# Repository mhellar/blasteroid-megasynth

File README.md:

# BLASTEROID MEGASYNTH

**Experimental industrial ambient on an ESP32-S3.** A slow machine drone you build from layers, two robot mouths
(**SAM**, the 1982 Software Automatic Mouth, and the **Talkie** Speak & Spell LPC voice) that can freeze into drones,
get scratched on a knob and talk to each other, a box of industrial noises, and a huge reverb "space". It runs on a
4x4 keypad, one rotary pot, a 128x128 OLED and a small speaker.

At boot it plays a generative splash that's different every time: two random geometry scenes (string-art mandala,
polygon rings, flow-field particles, a rotating tunnel, a 3D Lissajous knot), glitch cuts. Then everything converges
into **the Blasteroid**: a cyborg cyclops in wraparound shades. His eye charges up, two lasers burn
**BLASTEROID / MEGASYNTH** in from opposite ends, SAM says the name, and Talkie answers "OPERATIONAL".

The board is a single-sided PCB designed to be **milled on a desktop CNC**. The modules plug into headers or edge
pads, so there's no SMD soldering.

## What's in here

| Folder | Contents |
|---|---|
| `firmware/blasteroid_megasynth/` | The Blasteroid Megasynth sketch (Arduino), with SAM's C core and the Talkie vocabularies bundled alongside |
| `firmware/keypad_bringup/` | Bring-up test: I2C scan, every key plays a note, pot = volume. Flash this first |
| `firmware/short_finder/` | Finds pins shorted to GND or to each other on a freshly milled board (pull-ups only, safe) |
| `hardware/kicad/` | KiCad project for the board (rev B: pot standing under the OLED), custom symbols + footprints |
| `hardware/cnc/` | Gerbers + drills, G-code for a Genmitsu Cubiko (GRBL), FlatCAM script, 1:1 fit-test print, cheat sheet |
| `tools/` | `splash_preview.py`: a Python mirror of the boot splash that renders storyboards (`python splash_preview.py <seed> <seconds...>`, needs numpy + Pillow) |

## Parts

| Ref | Part | Notes |
|---|---|---|
| U1 | ESP32-S3 **SuperMini** | 2x 1x9 female headers. Needs **PSRAM** (e.g. 4 MB flash / 2 MB PSRAM) |
| U2 | MAX98357A I2S amp breakout | 1x7 female header, VIN on 5 V, plus a small 4-8 ohm speaker |
| U3 | 1.5" 128x128 OLED, **SH1107**, I2C | 1x4 female header (VCC GND SCL SDA) |
| U4 | 4x4 tact keypad module (passive matrix, e.g. QYF-JP01) | hangs off the bottom edge; its right-angle pins lie on 8 edge pads |
| U5 | 10k rotary pot module (3 pins) | stands in 3 holes under the OLED, knob towards the keypad |
| | 100 x 70 mm single-sided copper clad | board is 96 x 66 mm, M3 holes |

## Pinout

| Function | GPIO |
|---|---|
| OLED SDA / SCL | 9 / 8 |
| Amp DIN / BCLK / LRC | 43 (TX) / 44 (RX) / 1 |
| Keypad rows R1-R4 / columns C1-C4 | 2 3 4 5 / 6 7 13 12 |
| Pot wiper / pot high leg | 10 / 11 (driven HIGH as the pot's supply), low leg to GND |

The amp uses the TX/RX pins, so **USB CDC On Boot must be Enabled** (serial goes over native USB).

## Build the firmware

1. Arduino IDE (or arduino-cli) with the **ESP32 core 3.x** and the **U8g2** library.
2. Board settings: **ESP32S3 Dev Module**, **USB CDC On Boot: Enabled**, **PSRAM: enabled**.
   arduino-cli FQBN: `esp32:esp32:esp32s3:CDCOnBoot=cdc,PSRAM=enabled`
3. Flash `keypad_bringup` first to check the keys, pot, OLED and speaker, then `blasteroid_megasynth`.

```
arduino-cli compile --fqbn esp32:esp32:esp32s3:CDCOnBoot=cdc,PSRAM=enabled firmware/blasteroid_megasynth
arduino-cli upload  --fqbn esp32:esp32:esp32s3:CDCOnBoot=cdc,PSRAM=enabled -p COMx firmware/blasteroid_megasynth
```

Tips:
- The OLED needs the `U8G2_SH1107_PIMORONI_128X128` constructor. The generic SH1107 one shifts the picture by 32 px.
- If the SuperMini sits silent after an upload, press RST. The auto-reset can leave it in the bootloader.
- If the knob works backwards, turn the pot module round. Swapping its outer legs reverses the direction.

## Playing it

```
[MODE ] [ pad 0 ] [ pad 1 ] [ pad 2 ]      left column: tap = quick action,
[FX   ] [ pad 3 ] [ pad 4 ] [ pad 5 ]      HOLD = the screen shows what the 12 pads do
[SEQ  ] [ pad 6 ] [ pad 7 ] [ pad 8 ]
[SHIFT] [ pad 9 ] [ pad 10] [ pad 11]
```

| Key | tap | hold + pad |
|---|---|---|
| MODE | next mode (HUM > SAM > TALK > MACH) | modes, volume, Talkie bank, **REPLAY** the boot film, SAM voice (ROBOT SAM GHOST DEEP) |
| FX | next voice FX | CLEAN ECHO RADIO GRAIN DEEP VOX CHOIR, momentary STUTTER / REVERSE / TAPE STOP / UNDERWATER, **INFINITE** (reverb freeze) |
| SEQ | REC on/off | PLAY, **CROSSTALK**, AUTO, BPM -/+, MUTATE, RANDOM machines (sparse > busy > factory), clears, SILENCE |
| SHIFT | PLAY/STOP | per mode: drone octave / brightness / LFO speed / detune; SAM words backwards; Talkie bends; machine mutes |

**The knob**
- **Knob alone:** the current voice FX's main control: pitch, echo feedback, radio tuning, grain density, depth, vocoder wet, choir breath.
- **SHIFT + knob = SCRATCH:** scrub through the current SAM or Talkie word like a record under your hand. It's silent while the knob is still.
- **FX + knob = SPACE:** from dry and close to a huge, long reverb.

**Modes**
- **HUM:** drone layers on/off: MAINS (transformer hum), SUB, PAD, CHOIR (morphing vowel), METAL (inharmonic FM girder), WIND, RADIO (shortwave whistle and crackle), PULSE (heartbeat). Also DRIFT (the chord wanders i-bVI-bIII-bVII), KEY -/+, and CHORD (fifth, minor7, sus2, minor9, void).
- **SAM:** 12 words (OHM, SILENCE, SIGNAL, MACHINE, BREATHE, ECHO, VOID, DRIFT, STATIC, RESONANCE, FREQUENCY, WE ARE LISTENING). Tap = say it, hold = **freeze** it into a granular drone.
- **TALK:** four Talkie banks: SIGNAL, NUMBERS (numbers station), ELEMENTS, MACHINE. Tap = say it, hold = freeze the mouth on one frame, humming in the drone's key.
- **MACH:** 12 industrial sounds: KLANK, PIPE, HAMMER, HISS, GEIGER, RELAY, SERVO, SONAR, CHAIN, DRIP, HORN, THUD. Hold = repeat.
- **CROSSTALK:** SAM and Talkie take turns, a word per bar, over whatever is playing.
- With REC on, voices and machines are quantized into the 16-step sequencer.

## Make the board

Single-sided, all copper on **B.Cu**, made for isolation milling. The Gerbers also work at a board house as a 1-layer board.
Full steps are in `hardware/cnc/CNC_CHEATSHEET.txt`: V-bit isolation, 1.0 mm drill, 2.0 mm drill, outline score.
The keypad's pins solder flat onto edge pads, and the pot stands in 3 holes.

> **Isolation gutters:** with a single 0.1 mm V-bit pass, several SuperMini pads stayed shorted to the ground pour.
> `load_and_mirror.tcl` now isolates with **3 passes** (about a 0.3 mm gutter). The ready-made
> `1_isolation_0.1vbit.nc` is the older single-pass file, so regenerate it with FlatCAM (set the path at the top of
> the script). After milling, meter every header pad to GND before soldering, or flash `short_finder` on a
> populated board.

Print `PRINT_1to1_fit_test.pdf` at 100% and check your modules against it before milling. The keypad and pot
outlines were measured from photos.

## Credits and license

- **SAM** (Software Automatic Mouth) by Mark Barton / Don't Ask Software (1982). C port by Sebastian Macke,
  ESP8266SAM by Earle F. Philhower III.
- **Talkie** LPC speech by Peter Knight, extended by Armin Joachimsmeyer (vocabulary data bundled).
- **U8g2** by olikraus; **esp-dsp** and the ESP32 Arduino core by Espressif.
- Co-created by **Mark Hellar** and **Claude** (Anthropic). PCB milled and soldered by Mark Hellar.

Licensed under the **GNU GPL v3** (see `LICENSE`), matching the bundled SAM and Talkie code.

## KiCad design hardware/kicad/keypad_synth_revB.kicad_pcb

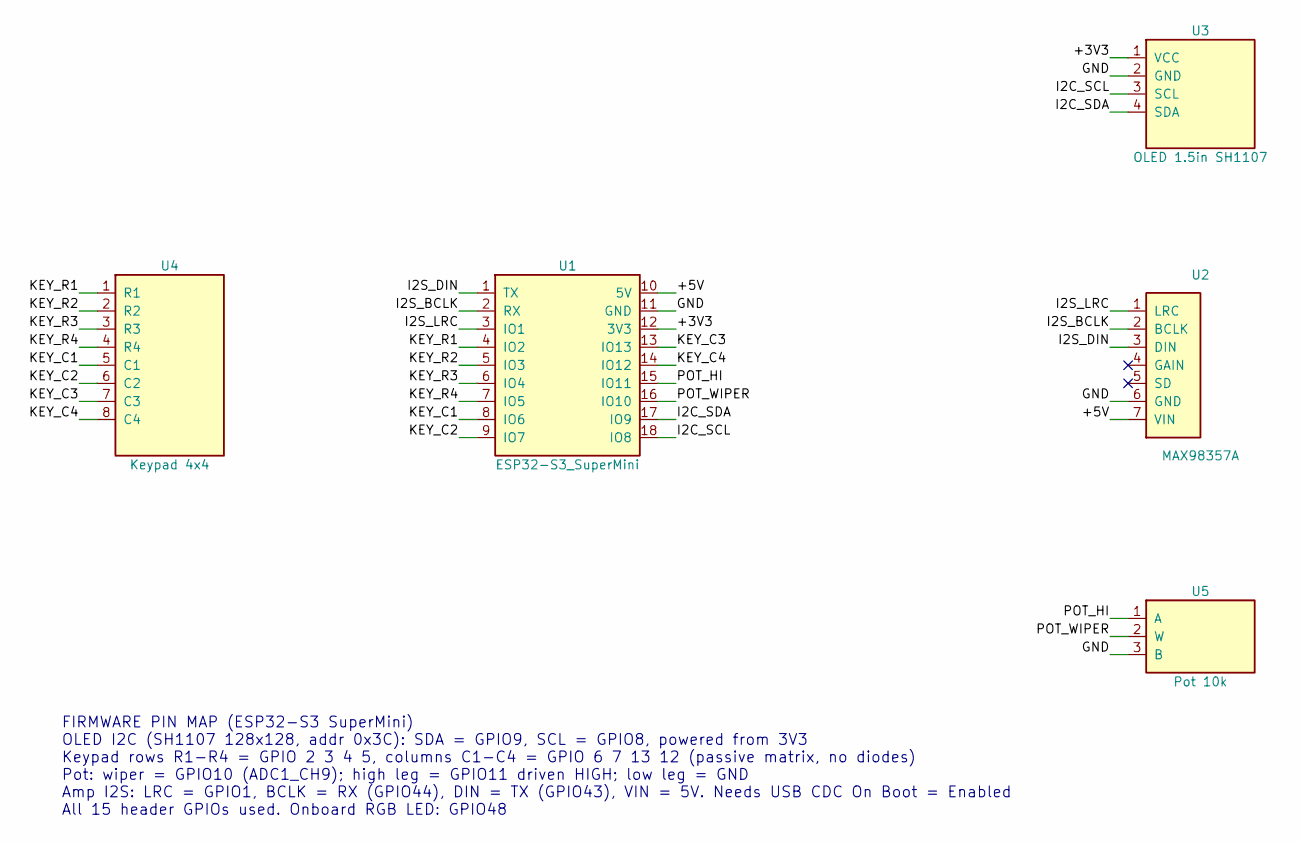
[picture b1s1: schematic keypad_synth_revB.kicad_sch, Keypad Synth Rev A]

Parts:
U1: ESP32-S3_SuperMini; ESP32-S3_SuperMini_CNC
U2: MAX98357A; MAX98357A_Module_CNC
U3: OLED 1.5in SH1107; OLED_1.5in_128x128_I2C_CNC
U4: Keypad 4x4; EdgePads_Keypad4x4_CNC
U5: Pot 10k; Pot_Standing_CNC

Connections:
/+3V3: U1.12 (3V3), U3.1 (VCC)
/+5V: U1.10 (5V), U2.7 (VIN)
/GND: U1.11 (GND), U2.6 (GND), U3.2 (GND), U5.3 (B)
/I2C_SCL: U1.18 (IO8), U3.3 (SCL)
/I2C_SDA: U1.17 (IO9), U3.4 (SDA)
/I2S_BCLK: U1.2 (RX), U2.2 (BCLK)
/I2S_DIN: U1.1 (TX), U2.3 (DIN)
/I2S_LRC: U1.3 (IO1), U2.1 (LRC)
/KEY_C1: U1.8 (IO6), U4.5 (C1)
/KEY_C2: U1.9 (IO7), U4.6 (C2)
/KEY_C3: U1.13 (IO13), U4.7 (C3)
/KEY_C4: U1.14 (IO12), U4.8 (C4)
/KEY_R1: U1.4 (IO2), U4.1 (R1)
/KEY_R2: U1.5 (IO3), U4.2 (R2)
/KEY_R3: U1.6 (IO4), U4.3 (R3)
/KEY_R4: U1.7 (IO5), U4.4 (R4)
/POT_HI: U1.15 (IO11), U5.1 (A)
/POT_WIPER: U1.16 (IO10), U5.2 (W)

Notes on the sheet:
FIRMWARE PIN MAP (ESP32-S3 SuperMini) OLED I2C (SH1107 128x128, addr 0x3C): SDA = GPIO9, SCL = GPIO8, powered from 3V3 Keypad rows R1-R4 = GPIO 2 3 4 5, columns C1-C4 = GPIO 6 7 13 12 (passive matrix, no diodes) Pot: wiper = GPIO10 (ADC1_CH9); high leg = GPIO11 driven HIGH; low leg = GND Amp I2S: L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

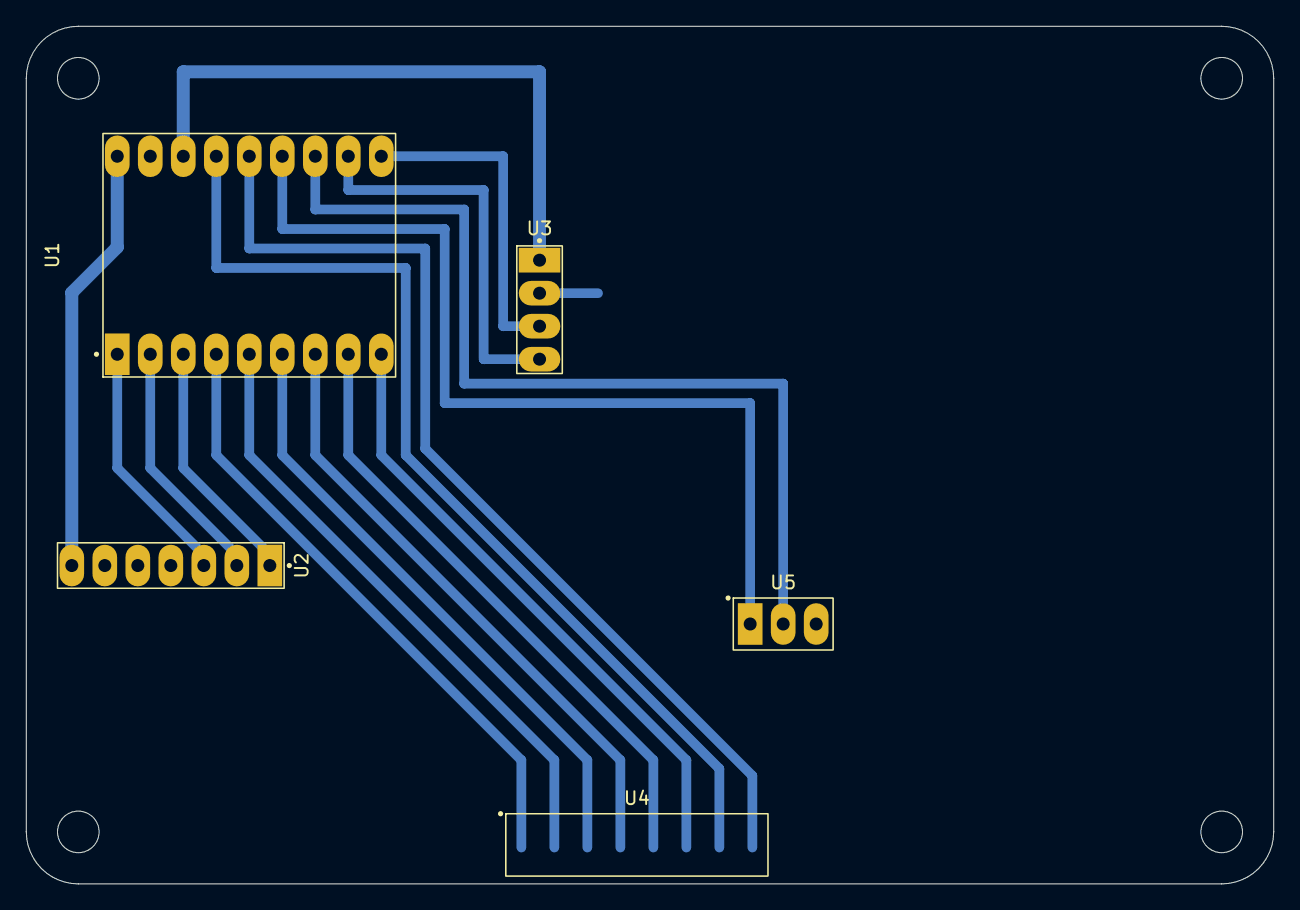
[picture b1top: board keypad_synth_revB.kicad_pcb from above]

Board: 2 copper layers, 96.0 x 66.0 mm, 9 parts (0 on the bottom side), 18 nets.

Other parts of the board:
H1, H2, H3, H4: MountingHole_3.2mm_M3
